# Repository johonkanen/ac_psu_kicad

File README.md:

# ac_psu_kicad

> **This is v6: the baseboard for six half-bridge power cards** (branch `v6-baseboard`, merged into main from
> 2026-11-24). The switches, gate drivers and switch nodes moved off this board onto six vertical cards
> (`johonkanen/hb_power_card`, branch `card-rev1`): two AFE legs, two inverter legs, DAB primary and secondary. The
> baseboard carries the bulk capacitors, filters, measurement, isolation, the aux flyback, the control card sockets,
> the card DC terminals / pigtails and CTRL headers, and the DC bus pours to them.
>
> **State (2026-11-24):** routing pass 1 is legal (DRC 0 shorts / 0 clearance errors, parity 0, domain gaps and both
> layout checks OK, no pour split, `tools/check_all.sh` passes); **102 connections are still open** and listed as
> pending: supplies and grounds to the headers and sense groups (about 52), the CTRL area under the control card
> (13), card PWM nets (12), the two sigma-delta links (7), and a few more; details at the top of `STATUS.md`.
> Plans: `V6_PLAN.md` (baseboard), the card's `CARD_REV1_PLAN.md`. Nothing here is ordered.
>
> **The v5 TO-247 layout is abandoned** (it did not route); it is kept on branch `v5-layout`. The text below
> describes the Proteus-to-KiCad migration this repository started with (v1 ... v5).

Migration of the **single_phase_inverter_psu_v3** board ("Inverter PSU") from Proteus 8.12
to KiCad 10. The KiCad schematic is redrawn from the Proteus PDF, and the PCB is rebuilt
from the Proteus gerbers, so that every pad, track, via and pour carries a net from the new
schematic. The goal is a KiCad design that is **electrically identical** to the Proteus
original.

The Proteus project file is binary and cannot be read, so the IPC-D-356A netlist in the
CADCAM export is the reference: 208 nets, 267 parts, 1075 pads, each with net, refdes, pin
and coordinates. Every check in this repo compares against that file.

- `PLAN.md`: the full plan, inventory of the source files, risks and model usage.
- `STATUS.md`: what is done, the last verification output, findings about the original
  design, and what comes next.
- `next_prompt.md`: the prompt for the next work session, replaced at the end of every
  phase.

## Board

<!-- board-plots:start -->
<!-- Generated by kicad-board-plots; edits between these markers are overwritten. -->

3D renders and copper layers of `kicad/ac_psu.kicad_pcb`, the layers in stack order without silkscreen. Plotted by [kicad-board-plots](https://github.com/johonkanen/kicad-board-plots) on each board change; the images live on the `renders` branch.

<table>
<tr>
<td align="center"><br><b>3D, top</b></td>
<td align="center"><br><b>3D, bottom (seen from below)</b></td>
</tr>
<tr>
<td align="center"><br><b>F.Cu: signal, FILTER_INPUT, DC+, GND, ISOPGND, DAB_GROUND and 14 more pours (top)</b></td>
<td align="center"><br><b>In1.Cu: signal, CTRLGND_A, ISOGND, SW_INV_B, AUX_DRAIN, FILTER_INPUT and 5 more pours</b></td>
</tr>
<tr>
<td align="center"><br><b>In2.Cu: signal, 3V3_ISO, INU_FILTER_INPUT, GND, ISOPGND, 3V3_CTRL and 5 more pours</b></td>
<td align="center"><br><b>In3.Cu: signal, DC+, ISODC+ pours</b></td>
</tr>
<tr>
<td align="center"><br><b>In4.Cu: signal, ISOGND, CTRLGND, ISOPGND, CTRLGND_A, GND and 1 more pours</b></td>
<td align="center"><br><b>B.Cu: signal, 15V_ISO, ISODC+, INDUCTOR_OUTPUT, JEE, AC_IN_1 and 4 more pours (bottom, seen from the top)</b></td>
</tr>
</table>

<!-- board-plots:end -->

## Layout

```
source/      Proteus exports (read-only): schematic PDF + page renders, CADCAM zip
             (gerbers, drill, IPC-D-356A netlist)
reference/   tables generated from the IPC netlist: pads (CSV/JSON), pin→net per part,
             pins per net
lib/         ac_psu.kicad_sym (project symbols, pin numbers = IPC pin ids),
             ac_psu.pretty (project footprints), part_map.csv (refdes → sheet, symbol,
             value), footprint_map.csv (refdes → footprint)
kicad/       KiCad project: root sheet + 11 hierarchical sheets, ac_psu.kicad_pcb
             (Proteus-generated up to tag proteus-conversion-complete, v4 edits by tools/v4/)
tools/       scripts and checks (see below)
reports/     generated reports: footprint fit, net assignment, pour nets (committed);
             ERC and DRC (not committed)
```

## Phases

| Phase | Content | State |
|---|---|---|
| 0 | Tooling: KiCad AppImage wrappers, IPC-D-356A parser, pin/net reference tables | done |
| 1 | Schematic: symbol library and part map, netlist comparison script, project skeleton, transcription of the 11 sheets from the PDF | done |
| 2 | Footprints for every symbol, pad numbers = IPC pin ids, checked by fitting footprint pads onto the IPC pad coordinates | done |
| 3 | PCB: place footprints at the Proteus positions, convert gerber tracks/vias/pours into KiCad tracks, vias and zones, assign nets by copper connectivity | done |
| 4 | Verification: schematic netlist ≡ IPC, DRC clean, gerber round-trip overlay, regenerated IPC-356 pad list diff | not started |

`STATUS.md` holds the current state; this table is only updated when a phase finishes.

## Requirements

- KiCad 10.0.7 AppImage at `~/kicad/kicad-10.0.7-x86_64.AppImage`. The scripts mount it
  on demand and use its `kicad-cli` and Python (with `pcbnew`). Do not run the AppImage
  with `--version`; it hangs.
- Python 3 for the plain scripts.

## Tools

The generic tools are the shared [proteus2kicad](https://github.com/johonkanen/proteus2kicad)
repository, a git submodule in `tools/p2k` (clone with `git clone --recurse-submodules`, or
run `git submodule update --init`). Board values (source files, refdes/net fix-ups, expected
counts, layers, outline) are in `p2k_config.py`. The scripts in `tools/` are the ones not
moved yet; they import the shared modules from `p2k`. Wrappers: `tools/p2k/bin/p2k <tool>`,
`tools/p2k/bin/kipy` (KiCad's Python with pcbnew), `tools/p2k/bin/kicad-cli`.
The generic migration method distilled from this board, the playbook, is in proteus2kicad
(`tools/p2k/CONVERSION_PLAYBOOK.md`).

## Checks

Run everything with one command:

```sh
tools/check_all.sh
```

It runs:

| Step | Script |
|---|---|
| KiCad environment (pcbnew 10.0.7 loads) | `tools/p2k/bin/kipy` |
| IPC parser self-check | `tools/p2k/bin/p2k ipc356 --check` |
| Gerber X2 flashes and drills vs IPC, outline | `tools/p2k/bin/p2k check_sources` |
| Symbol library is up to date with its generator | `tools/gen_symbols.py --check` |
| Symbol pin sets match the IPC pins for every refdes (+ v4 deviations) | `tools/check_symbols_v4.py` |
| ERC | `tools/erc.sh` (report in `reports/erc.rpt`) |
| Schematic netlist vs IPC netlist (+ v4 deviations, values) | `tools/compare_netlists_v4.py` |
| Footprint library and map are up to date | `tools/gen_footprints.py --check` |
| Footprint pads fit the IPC pads (≤ 0.05 mm) | `tools/check_footprints.py --pcbnew` |
| Board pads/holes/vias vs IPC (position and net) | `tools/check_board.py` |
| Copper connectivity after zone fill: 0 shorts, 0 opens, every item on its group's net | `tools/assign_nets.py --check` |
| DRC with schematic parity: 0 shorts, 0 unconnected | `tools/drc.py` (report in `reports/drc.json`) |
| Domain net classes / DRC rules match the schematic (IEC 61010-1 gaps P, I, C, E) | `tools/v4/domain_rules.py --check` |
| Insulation spacing between the domains on every layer | `tools/v4/domain_gaps.py` |
| IPC-D-356 export vs Proteus, gerber round trip | `tools/ipc356_diff.py`, `tools/gerber_roundtrip.py --check` |

`p2k compare_netlists` exports the KiCad netlist and compares nets as sets of
(refdes, pin), so net names do not have to match. It reports pins on the wrong net, merged
or split nets, N/C mismatches, missing or extra parts and pins, and progress per sheet.
Use `--sheet N` to check one sheet while drawing.

Other tools: `gen_symbols.py` builds `lib/ac_psu.kicad_sym` from KiCad standard symbols
and box symbols (helpers in `p2k.symgen`); `p2k.sch_builder` is a small library for writing schematic sheets from
Python; `p2k.sexpr` reads and writes KiCad s-expression files; `p2k make_skeleton` created
the project skeleton once; `tools/sheets/sheetNN.py` generate the 11 sheets.

**v5** (aux flyback, control-card isolation; V5_PLAN.md, CTRL_ISOLATION_PLAN.md): parts in
`tools/v5/v5_parts.py`, deviations in `lib/v5_deviations.csv` / `lib/v5_copper.csv` (kinds remove,
rename, and pending-layout areas where the checks list items as pending), board step
`tools/v5/v5_1_aux_ctrl.py`; the layout itself is done in the KiCad GUI.

**Since v4 the design board `kicad/ac_psu.kicad_pcb` is frozen**: it is edited directly by small
committed pcbnew scripts (`tools/v4/fix_*.py`, see STATUS.md "v4 design fixes"), and the Proteus
comparisons apply exactly the deviations listed in `lib/v4_deviations.csv` / `lib/v4_copper.csv`
(`tools/deviations.py`; wrappers `tools/compare_netlists_v4.py`, `tools/check_symbols_v4.py`).
`tools/make_pcb.sh` now rebuilds the *Proteus* board from the schematic at tag
`proteus-conversion-complete` into `build/proteus/` (regression check of the conversion tools,
`tools/regen_check.sh`). The Proteus board was built with `tools/make_pcb.sh`: `build_pcb.py` (footprints, nets, outline,
mounting holes), `gerber_to_tracks.py` (Proteus copper gerbers → tracks and vias, using
`p2k.gerber`), `assign_nets.py` (nets by copper connectivity, `p2k.geom2d`) and
`pours_to_zones.py` (Proteus pours → filled zones). The output is reproducible byte for byte.

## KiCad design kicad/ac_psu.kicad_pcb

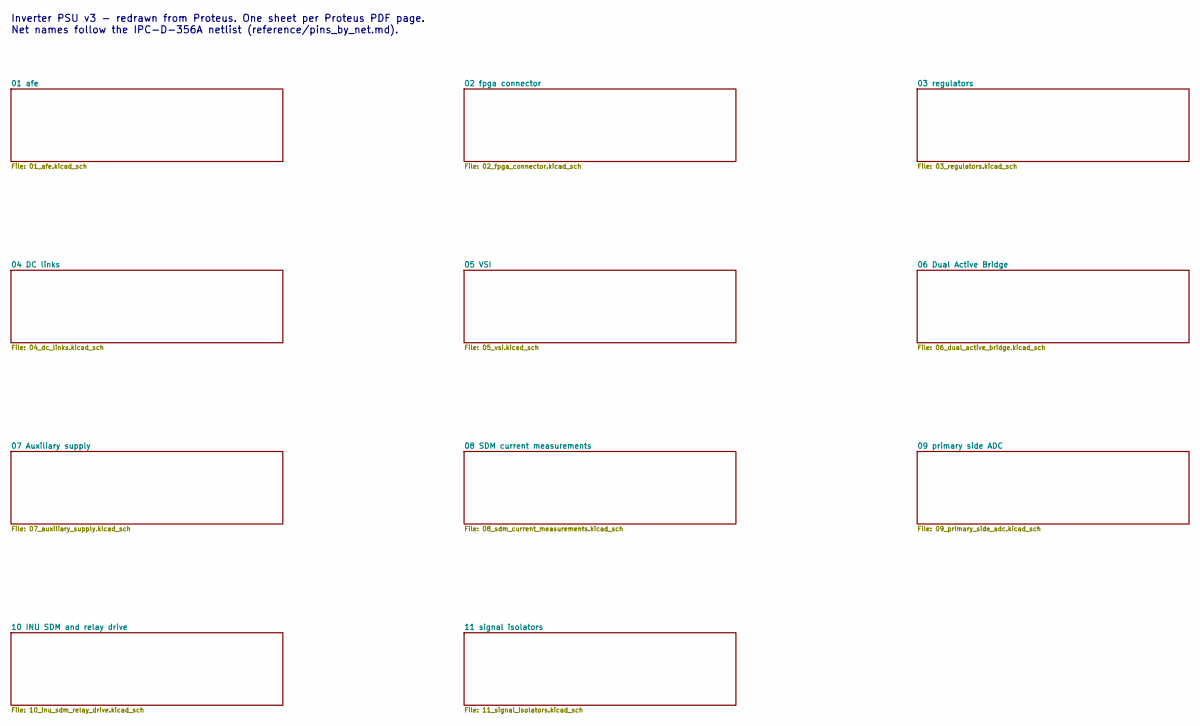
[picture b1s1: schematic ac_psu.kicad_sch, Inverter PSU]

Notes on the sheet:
Inverter PSU v3 - redrawn from Proteus. One sheet per Proteus PDF page. Net names follow the IPC-D-356A netlist (reference/pins_by_net.md).

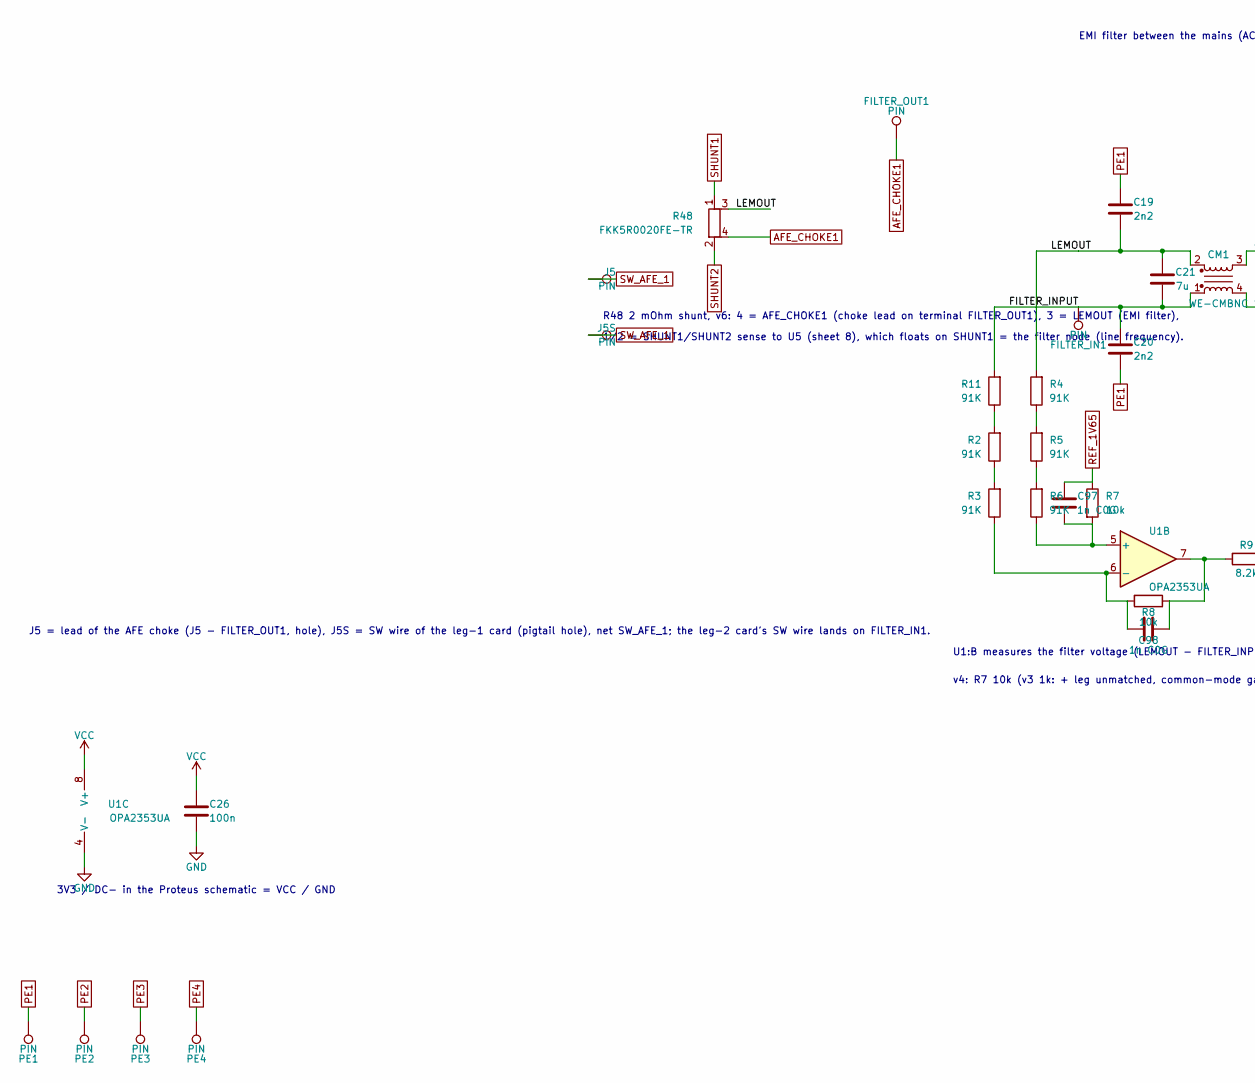
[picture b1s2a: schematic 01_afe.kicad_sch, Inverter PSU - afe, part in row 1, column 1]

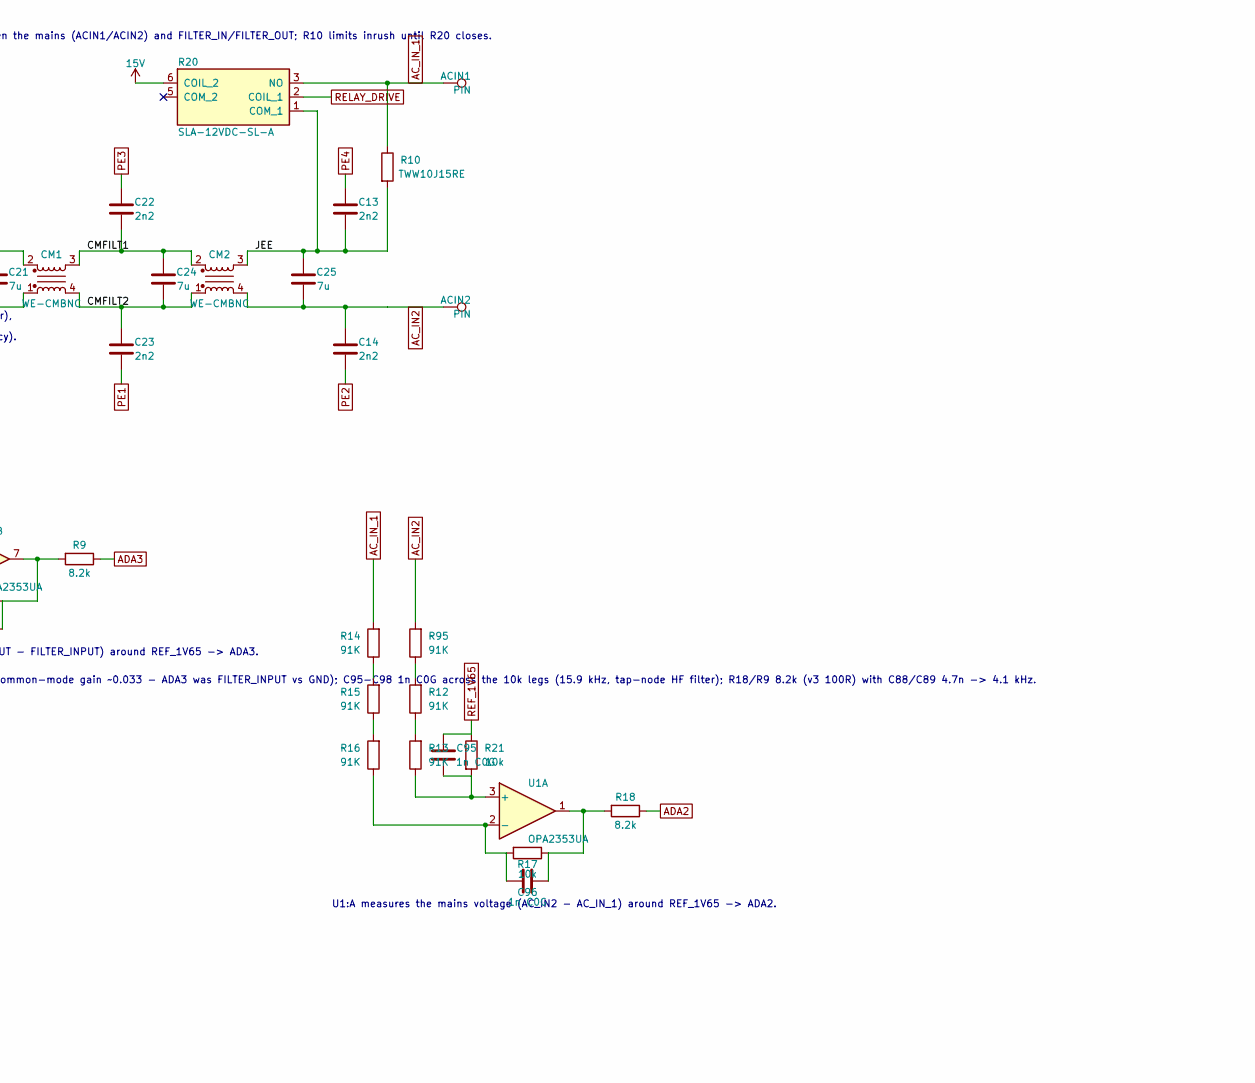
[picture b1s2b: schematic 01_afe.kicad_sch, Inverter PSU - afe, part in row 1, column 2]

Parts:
ACIN1, ACIN2: PIN; Terminal_2x1_P5.00mm_D2.0mm_Drill1.4mm
C13, C14, C19, C20, C22, C23: 2n2; C_Disc_D12.5mm_W5.0mm_P7.50mm
C21, C25: 7u; C_Rect_L33.0mm_W20.0mm_P27.50mm_MKS4_Proteus
C24: 7u; C_Rect_L33.0mm_W20.0mm_P27.50mm_MKS4
C26: 100n; C_0402_1005Metric
C95, C96, C97, C98: 1n C0G; C_0402_1005Metric
CM1, CM2: WE-CMBNC; L_CommonMode_WE-CMBNC
FILTER_IN1: PIN; WirePigtail_D6.0mm_Drill3.0mm
FILTER_OUT1: PIN; WireHole_D5.0mm_Drill2.3mm
J5: PIN; WireHole_D5.0mm_Drill2.3mm
J5S: PIN; WirePigtail_D6.0mm_Drill3.0mm
PE1, PE2, PE3, PE4: PIN; Terminal_D4.0mm_Drill3.0mm
R2, R3, R4, R5, R6, R11, R12, R13, R14, R15, R16, R95: 91K; R_1206_3216Metric_Pad1.30x1.75mm_HandSolder
R7, R8, R17, R21: 10k; R_0402_1005Metric
R9, R18: 8.2k; R_0402_1005Metric
R10: TWW10J15RE; R_Radial_Power_L13.0mm_W9.0mm_P5.00mm
R20: SLA-12VDC-SL-A; Relay_SLA-12VDC-SL-A
R48: FKK5R0020FE-TR; R_Shunt_FKK5R0020FE
U1: OPA2353UA; TSSOP-8_3x3mm_P0.65mm_Proteus

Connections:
15V: R20.6 (COIL_2); also elsewhere on the board
/01 afe/CMFILT1: C22.2, C24.1, CM1.3, CM2.2
/01 afe/CMFILT2: C23.2, C24.2, CM1.4, CM2.1
/01 afe/FILTER_INPUT: C20.2, C21.2, CM1.1, FILTER_IN1.1, R11.2
/01 afe/JEE: C13.2, C25.1, CM2.3, R10.2, R20.1 (COM_1)
/01 afe/LEMOUT: C19.2, C21.1, CM1.2, R4.2, R48.3
AC_IN2: ACIN2.1, C14.2, C25.2, CM2.4, R95.2
AC_IN_1: ACIN1.1, R10.1, R14.2, R20.3 (NO)
ADA2: R18.1; also elsewhere on the board
ADA3: R9.1; also elsewhere on the board
AFE_CHOKE1: FILTER_OUT1.1, R48.4
GND: C26.1, U1.4 (V-); also elsewhere on the board
unnamed: C96.1, R17.1, R18.2, U1.1
unnamed: C98.1, R8.1, R9.2, U1.7
unnamed: R2.1, R3.2
unnamed: R4.1, R5.2
unnamed: R5.1, R6.2
unnamed: R2.2, R11.1
unnamed: R12.1, R13.2
unnamed: R12.2, R95.1
unnamed: R14.1, R15.2
unnamed: R15.1, R16.2
unnamed: C95.2, R13.1, R21.2, U1.3 (+)
unnamed: C96.2, R16.1, R17.2, U1.2 (-)
unnamed: C97.2, R6.1, R7.2, U1.5 (+)
unnamed: C98.2, R3.1, R8.2, U1.6 (-)
PE1: C19.1, C20.1, C23.1, PE1.1
PE2: C14.1, PE2.1
PE3: C22.1, PE3.1
PE4: C13.1, PE4.1
REF_1V65: C95.1, C97.1, R7.1, R21.1; also elsewhere on the board
RELAY_DRIVE: R20.2 (COIL_1); also elsewhere on the board
SHUNT1: R48.1; also elsewhere on the board
SHUNT2: R48.2; also elsewhere on the board
SW_AFE_1: J5.1, J5S.1
VCC: C26.2, U1.8 (V+); also elsewhere on the board

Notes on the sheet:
J5 = lead of the AFE choke (J5 - FILTER_OUT1, hole), J5S = SW wire of the leg-1 card (pigtail hole), net SW_AFE_1; the leg-2 card's SW wire lands on FILTER_IN1.
R48 2 mOhm shunt, v6: 4 = AFE_CHOKE1 (choke lead on terminal FILTER_OUT1), 3 = LEMOUT (EMI filter),
1/2 = SHUNT1/SHUNT2 sense to U5 (sheet 8), which floats on SHUNT1 = the filter node (line frequency).
EMI filter between the mains (ACIN1/ACIN2) and FILTER_IN/FILTER_OUT; R10 limits inrush until R20 closes.
U1:B measures the filter voltage (LEMOUT - FILTER_INPUT) around REF_1V65 -> ADA3.
v4: R7 10k (v3 1k: + leg unmatched, common-mode gain ~0.033 - ADA3 was FILTER_INPUT vs GND); C95-C98 1n C0G across the 10k legs (15.9 kHz, tap-node HF filter); R18/R9 8.2k (v3 100R) with C88/C89 4.7n -> 4.1 kHz.
U1:A measures the mains voltage (AC_IN2 - AC_IN_1) around REF_1V65 -> ADA2.
3V3 / DC- in the Proteus schematic = VCC / GND

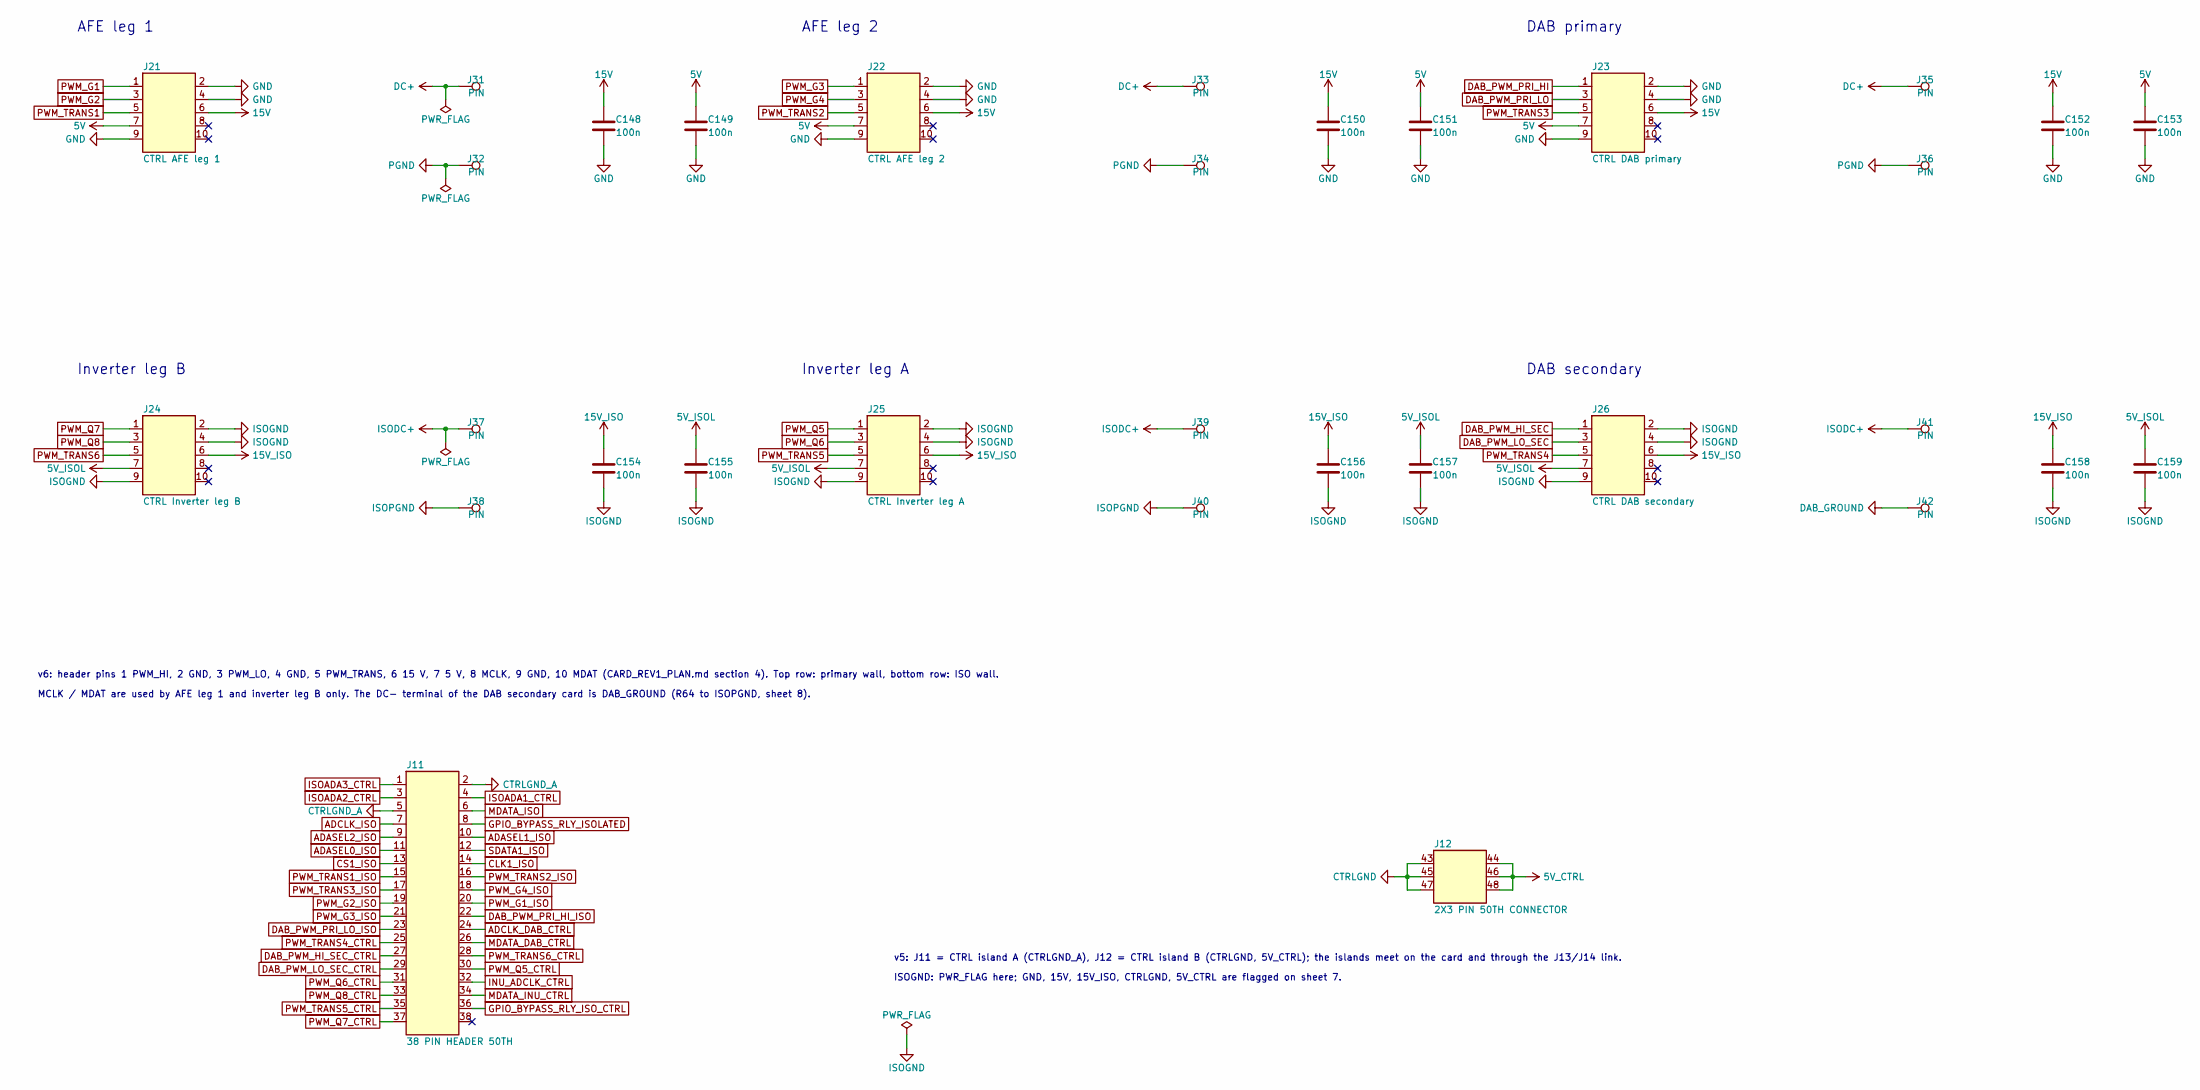
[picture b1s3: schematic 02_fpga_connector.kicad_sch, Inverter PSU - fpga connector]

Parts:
C148, C149, C150, C151, C152, C153, C154, C155, C156, C157, C158, C159: 100n; C_0603_1608Metric
J11: 38 PIN HEADER 50TH; PinHeader_2x19_P1.27mm_Vertical_Proteus
J12: 2X3 PIN 50TH CONNECTOR; PinHeader_2x03_P1.27mm_Vertical_Pins43-48
J21: CTRL AFE leg 1; Samtec_SHF-105-01-L-D-TH
J22: CTRL AFE leg 2; Samtec_SHF-105-01-L-D-TH
J23: CTRL DAB primary; Samtec_SHF-105-01-L-D-TH
J24: CTRL Inverter leg B; Samtec_SHF-105-01-L-D-TH
J25: CTRL Inverter leg A; Samtec_SHF-105-01-L-D-TH
J26: CTRL DAB secondary; Samtec_SHF-105-01-L-D-TH
J31, J32, J33, J34, J35, J36, J37, J38: PIN; Wuerth_REDCUBE-PressFit_7462810_M3
J39, J40, J41, J42: PIN; WirePigtail_D6.0mm_Drill3.0mm

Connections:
5V: C149.1, C151.1, C153.1, J21.7, J22.7, J23.7; also elsewhere on the board
5V_CTRL: J12.44, J12.46, J12.48; also elsewhere on the board
5V_ISOL: C155.1, C157.1, C159.1, J24.7, J25.7, J26.7; also elsewhere on the board
15V: C148.1, C150.1, C152.1, J21.6, J22.6, J23.6; also elsewhere on the board
15V_ISO: C154.1, C156.1, C158.1, J24.6, J25.6, J26.6; also elsewhere on the board
ADASEL0_ISO: J11.11; also elsewhere on the board
ADASEL1_ISO: J11.10; also elsewhere on the board
ADASEL2_ISO: J11.9; also elsewhere on the board
ADCLK_DAB_CTRL: J11.24; also elsewhere on the board
ADCLK_ISO: J11.7; also elsewhere on the board
CLK1_ISO: J11.14; also elsewhere on the board
CS1_ISO: J11.13; also elsewhere on the board
CTRLGND: J12.43, J12.45, J12.47; also elsewhere on the board
CTRLGND_A: J11.2, J11.5; also elsewhere on the board
DAB_GROUND: J42.1; also elsewhere on the board
DAB_PWM_HI_SEC: J26.1; also elsewhere on the board
DAB_PWM_HI_SEC_CTRL: J11.27; also elsewhere on the board
DAB_PWM_LO_SEC: J26.3; also elsewhere on the board
DAB_PWM_LO_SEC_CTRL: J11.29; also elsewhere on the board
DAB_PWM_PRI_HI: J23.1; also elsewhere on the board
DAB_PWM_PRI_HI_ISO: J11.22; also elsewhere on the board
DAB_PWM_PRI_LO: J23.3; also elsewhere on the board
DAB_PWM_PRI_LO_ISO: J11.23; also elsewhere on the board
DC+: J31.1, J33.1, J35.1; also elsewhere on the board
GND: C148.2, C149.2, C150.2, C151.2, C152.2, C153.2, J21.2, J21.4, J21.9, J22.2, J22.4, J22.9, J23.2, J23.4, J23.9; also elsewhere on the board
GPIO_BYPASS_RLY_ISOLATED: J11.8; also elsewhere on the board
GPIO_BYPASS_RLY_ISO_CTRL: J11.36; also elsewhere on the board
INU_ADCLK_CTRL: J11.32; also elsewhere on the board
ISOADA1_CTRL: J11.4; also elsewhere on the board
ISOADA2_CTRL: J11.3; also elsewhere on the board
ISOADA3_CTRL: J11.1; also elsewhere on the board
ISODC+: J37.1, J39.1, J41.1; also elsewhere on the board
ISOGND: C154.2, C155.2, C156.2, C157.2, C158.2, C159.2, J24.2, J24.4, J24.9, J25.2, J25.4, J25.9, J26.2, J26.4, J26.9; also elsewhere on the board
ISOPGND: J38.1, J40.1; also elsewhere on the board
MDATA_DAB_CTRL: J11.26; also elsewhere on the board
MDATA_INU_CTRL: J11.34; also elsewhere on the board
MDATA_ISO: J11.6; also elsewhere on the board
PGND: J32.1, J34.1, J36.1; also elsewhere on the board
PWM_G1: J21.1; also elsewhere on the board
PWM_G1_ISO: J11.20; also elsewhere on the board
PWM_G2: J21.3; also elsewhere on the board
PWM_G2_ISO: J11.19; also elsewhere on the board
PWM_G3: J22.1; also elsewhere on the board
PWM_G3_ISO: J11.21; also elsewhere on the board
PWM_G4: J22.3; also elsewhere on the board
PWM_G4_ISO: J11.18; also elsewhere on the board
PWM_Q5: J25.1; also elsewhere on the board
PWM_Q5_CTRL: J11.30; also elsewhere on the board
PWM_Q6: J25.3; also elsewhere on the board
PWM_Q6_CTRL: J11.31; also elsewhere on the board
PWM_Q7: J24.1; also elsewhere on the board
PWM_Q7_CTRL: J11.37; also elsewhere on the board
PWM_Q8: J24.3; also elsewhere on the board
PWM_Q8_CTRL: J11.33; also elsewhere on the board
PWM_TRANS1: J21.5; also elsewhere on the board
PWM_TRANS1_ISO: J11.15; also elsewhere on the board
PWM_TRANS2: J22.5; also elsewhere on the board
PWM_TRANS2_ISO: J11.16; also elsewhere on the board
PWM_TRANS3: J23.5; also elsewhere on the board
PWM_TRANS3_ISO: J11.17; also elsewhere on the board
PWM_TRANS4: J26.5; also elsewhere on the board
PWM_TRANS4_CTRL: J11.25; also elsewhere on the board
PWM_TRANS5: J25.5; also elsewhere on the board
PWM_TRANS5_CTRL: J11.35; also elsewhere on the board
PWM_TRANS6: J24.5; also elsewhere on the board
PWM_TRANS6_CTRL: J11.28; also elsewhere on the board
SDATA1_ISO: J11.12; also elsewhere on the board

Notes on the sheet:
AFE leg 1
AFE leg 2
DAB primary
Inverter leg B
Inverter leg A
DAB secondary
v6: header pins 1 PWM_HI, 2 GND, 3 PWM_LO, 4 GND, 5 PWM_TRANS, 6 15 V, 7 5 V, 8 MCLK, 9 GND, 10 MDAT (CARD_REV1_PLAN.md section 4). Top row: primary wall, bottom row: ISO wall.
MCLK / MDAT are used by AFE leg 1 and inverter leg B only. The DC- terminal of the DAB secondary card is DAB_GROUND (R64 to ISOPGND, sheet 8).
v5: J11 = CTRL island A (CTRLGND_A), J12 = CTRL island B (CTRLGND, 5V_CTRL); the islands meet on the card and through the J13/J14 link.
ISOGND: PWR_FLAG here; GND, 15V, 15V_ISO, CTRLGND, 5V_CTRL are flagged on sheet 7.

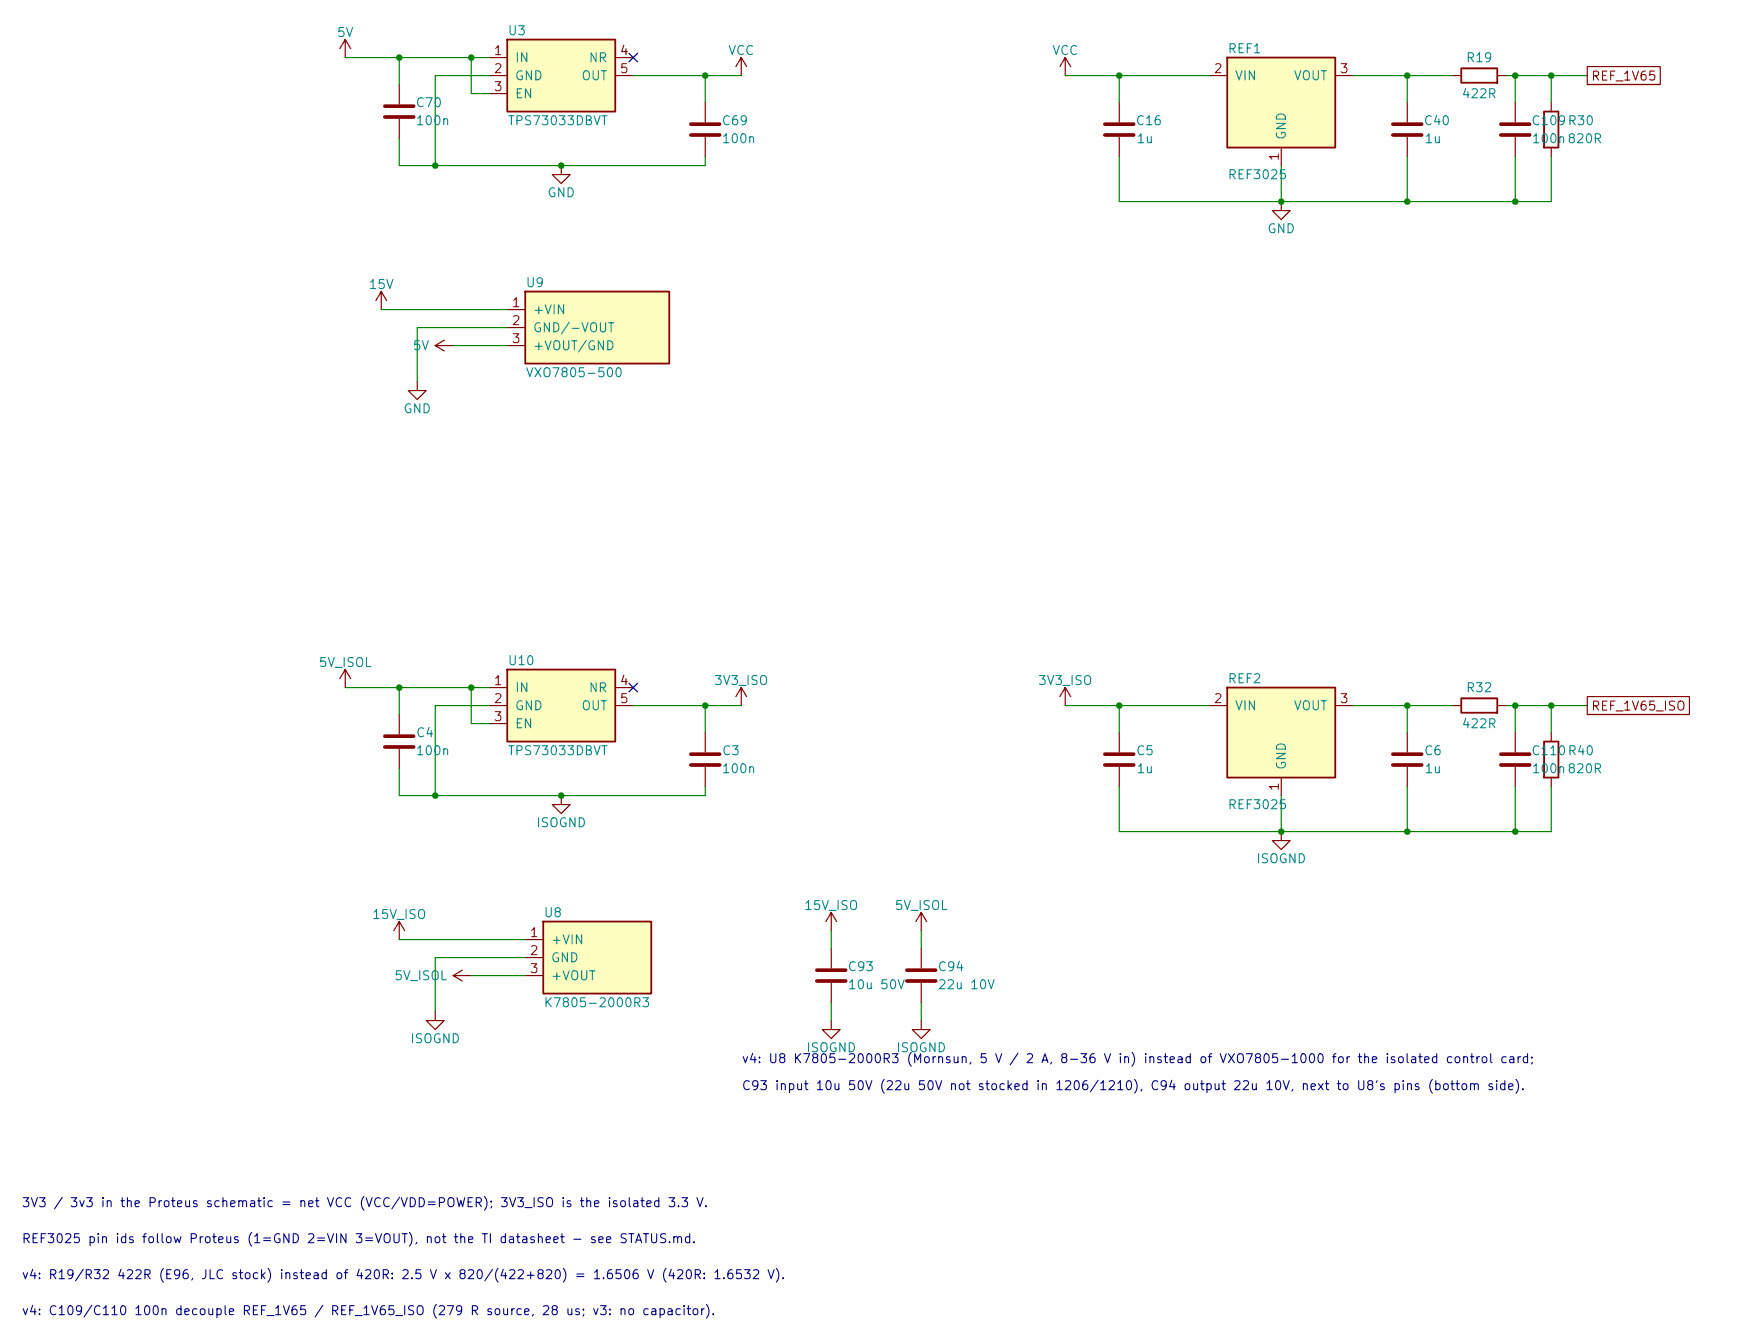
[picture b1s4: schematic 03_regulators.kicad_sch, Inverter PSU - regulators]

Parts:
C3, C4, C69, C70, C109, C110: 100n; C_0402_1005Metric
C5, C6, C16, C40: 1u; C_0402_1005Metric
C93: 10u 50V; C_1210_3225Metric
C94: 22u 10V; C_0805_2012Metric
R19, R32: 422R; R_0402_1005Metric
R30, R40: 820R; R_0402_1005Metric
REF1, REF2: REF3025; SOT-23_Proteus
U3, U10: TPS73033DBVT; SOT-23-5_TPS73033
U8: K7805-2000R3; Converter_DCDC_RECOM_R-78E-0.5_THT_Proteus
U9: VXO7805-500; Converter_DCDC_RECOM_R-78E-0.5_THT_Proteus

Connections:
3V3_ISO: C3.2, C5.2, REF2.2 (VIN), U10.5 (OUT); also elsewhere on the board
5V: C70.2, U3.1 (IN), U3.3 (EN), U9.3 (+VOUT/GND); also elsewhere on the board
5V_ISOL: C4.2, C94.1, U8.3 (+VOUT), U10.1 (IN), U10.3 (EN); also elsewhere on the board
15V: U9.1 (+VIN); also elsewhere on the board
15V_ISO: C93.1, U8.1 (+VIN); also elsewhere on the board
GND: C16.1, C40.1, C69.1, C70.1, C109.2, R30.2, REF1.1 (GND), U3.2 (GND), U9.2 (GND/-VOUT); also elsewhere on the board
ISOGND: C3.1, C4.1, C5.1, C6.1, C93.2, C94.2, C110.2, R40.2, REF2.1 (GND), U8.2 (GND), U10.2 (GND); also elsewhere on the board
unnamed: C40.2, R19.1, REF1.3 (VOUT)
unnamed: C6.2, R32.1, REF2.3 (VOUT)
REF_1V65: C109.1, R19.2, R30.1; also elsewhere on the board
REF_1V65_ISO: C110.1, R32.2, R40.1; also elsewhere on the board
VCC: C16.2, C69.2, REF1.2 (VIN), U3.5 (OUT); also elsewhere on the board

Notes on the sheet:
v4: U8 K7805-2000R3 (Mornsun, 5 V / 2 A, 8-36 V in) instead of VXO7805-1000 for the isolated control card;
C93 input 10u 50V (22u 50V not stocked in 1206/1210), C94 output 22u 10V, next to U8's pins (bottom side).
3V3 / 3v3 in the Proteus schematic = net VCC (VCC/VDD=POWER); 3V3_ISO is the isolated 3.3 V.
REF3025 pin ids follow Proteus (1=GND 2=VIN 3=VOUT), not the TI datasheet - see STATUS.md.
v4: R19/R32 422R (E96, JLC stock) instead of 420R: 2.5 V x 820/(422+820) = 1.6506 V (420R: 1.6532 V).
v4: C109/C110 100n decouple REF_1V65 / REF_1V65_ISO (279 R source, 28 us; v3: no capacitor).

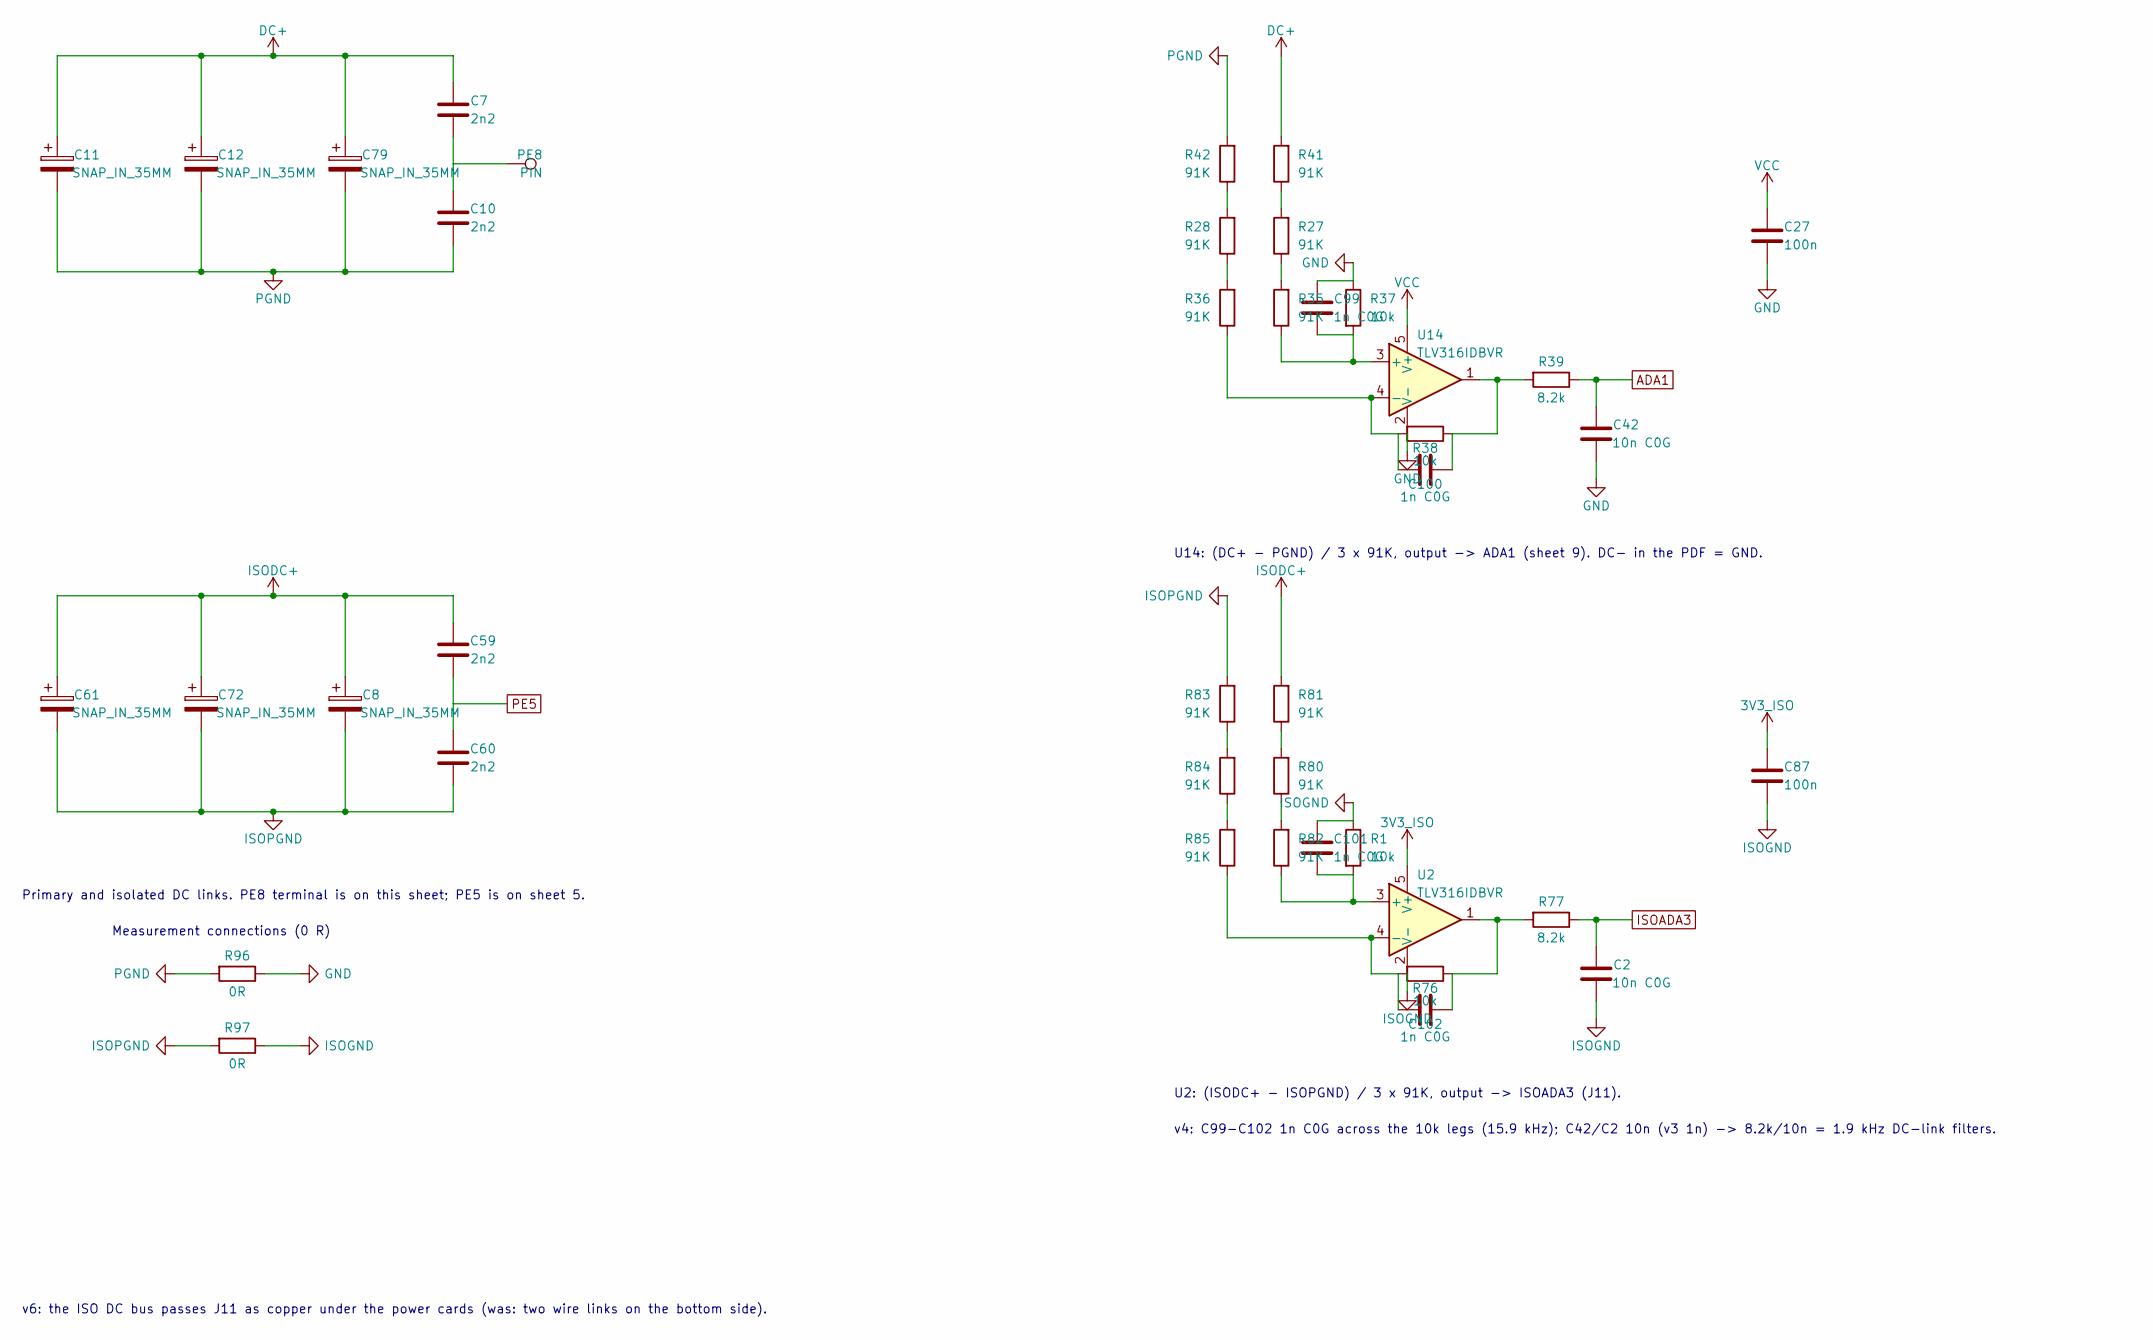
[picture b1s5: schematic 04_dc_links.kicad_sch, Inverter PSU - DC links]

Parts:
C2, C42: 10n C0G; C_0402_1005Metric
C7, C10, C59, C60: 2n2; C_Disc_D12.5mm_W5.0mm_P7.50mm
C8, C11, C12, C61, C72, C79: SNAP_IN_35MM; CP_Radial_D35.0mm_P10.00mm_SnapIn_Proteus
C27, C87: 100n; C_0402_1005Metric
C99, C100, C101, C102: 1n C0G; C_0402_1005Metric
PE8: PIN; Terminal_D4.0mm_Drill3.0mm
R1, R37, R38, R76: 10k; R_0402_1005Metric
R27, R28, R35, R36, R41, R42, R80, R81, R82, R83, R84, R85: 91K; R_1206_3216Metric_Pad1.30x1.75mm_HandSolder
R39, R77: 8.2k; R_0402_1005Metric
R96, R97: 0R; R_1206_3216Metric_Pad1.30x1.75mm_HandSolder
U2, U14: TLV316IDBVR; SOT-23-5_TLV316

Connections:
3V3_ISO: C87.2, U2.5 (V+); also elsewhere on the board
ADA1: C42.1, R39.1; also elsewhere on the board
DC+: C7.2, C11.1, C12.1, C79.1, R41.2; also elsewhere on the board
GND: C27.1, C42.2, C99.1, R37.1, R96.1, U14.2 (V-); also elsewhere on the board
ISOADA3: C2.1, R77.1; also elsewhere on the board
ISODC+: C8.1, C59.2, C61.1, C72.1, R81.2; also elsewhere on the board
ISOGND: C2.2, C87.1, C101.1, R1.1, R97.1, U2.2 (V-); also elsewhere on the board
ISOPGND: C8.2, C60.1, C61.2, C72.2, R83.2, R97.2; also elsewhere on the board
unnamed: C7.1, C10.2, PE8.1
unnamed: C100.1, R38.1, R39.2, U14.1
unnamed: C102.1, R76.1, R77.2, U2.1
unnamed: R27.1, R35.2
unnamed: R27.2, R41.1
unnamed: R28.1, R36.2
unnamed: R28.2, R42.1
unnamed: R80.1, R82.2
unnamed: R80.2, R81.1
unnamed: R83.1, R84.2
unnamed: R84.1, R85.2
unnamed: C101.2, R1.2, R82.1, U2.3 (+)
unnamed: C102.2, R76.2, R85.1, U2.4 (-)
unnamed: C99.2, R35.1, R37.2, U14.3 (+)
unnamed: C100.2, R36.1, R38.2, U14.4 (-)
PE5: C59.1, C60.2; also elsewhere on the board
PGND: C10.1, C11.2, C12.2, C79.2, R42.2, R96.2; also elsewhere on the board
VCC: C27.2, U14.5 (V+); also elsewhere on the board

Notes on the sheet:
Primary and isolated DC links. PE8 terminal is on this sheet; PE5 is on sheet 5.
Measurement connections (0 R)
U14: (DC+ - PGND) / 3 x 91K, output -> ADA1 (sheet 9). DC- in the PDF = GND.
U2: (ISODC+ - ISOPGND) / 3 x 91K, output -> ISOADA3 (J11).
v4: C99-C102 1n C0G across the 10k legs (15.9 kHz); C42/C2 10n (v3 1n) -> 8.2k/10n = 1.9 kHz DC-link filters.
v6: the ISO DC bus passes J11 as copper under the power cards (was: two wire links on the bottom side).
